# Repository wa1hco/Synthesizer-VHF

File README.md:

# Synthesizer-VHF

An ADF4351 synthesizer, 35 MHz to 4.4 GHz, with an ATtiny3216-M and USB. This branch, `hammond-1550Q`, is the Hammond 1550Q version: the board is the lid of the box. Designed by Jeffrey Millar (WA1HCO).

The first board in this repository was built and sent to fab with a TCXO, two RF outputs, USB serial, and a 12 V input. SPI between the microcontroller and the PLL is wired to ordinary pins, and the firmware bit-bangs it. That built board is the `as-built` branch. `main` carries the later layout of that same board, including the four-layer stackup and the 50 ohm coplanar RF routes. `hammond-1550Q` is the new enclosure and a new 10 MHz reference chain. It has not been built. The previous lid design remains on `diecast-2x2`.

Open the board from `hardware/Synthesizer-VHF.kicad_pro`. The project is KiCad 10.

## hammond-1550Q

The PCB is the lid of a Hammond 1550Q. Parts sit on the inside face. The SMA connectors sit on the outside face. USB-C J1 is on the inside face and does not overhang the outline. A contact strip on the rim ties the board ground to the box. Four mounting holes (H1–H4) match the 1550Q M3.5-0.6 pattern, 50 mm by 45 mm, with 4.10 mm clearance holes, and are bonded to ground.

The synthesizer is an ADF4351. Its VCO covers 2.2–4.4 GHz, and the on-chip divider brings the outputs down to 35 MHz. Two RF jacks leave the box.

The reference is an external 10 MHz on REF IN, shared when several boards must stay together. An on-board 10 MHz TCXO is the fallback. REF IN is 51 ohm and is squared before a 2:1 mux; the TCXO is squared the same way and is the other mux input. With no firmware, a pulldown on PA6 selects the TCXO. Firmware counts edges on PA5 to see that an external reference is present, then drives PA6 to select it. There is no ADF4002 and no REF OUT.

The schematic controller value is ATtiny3216-M. The footprint is the ATtiny1616 VQFN-20, 3 mm by 3 mm. ATtiny3216-M is not sold in that package. The symbol is still ATtiny1616-M. Its description says 32 kB flash. ATtiny3226-MF fits this footprint and has 32 kB flash. It is not a hex drop-in. The firmware still builds for an ATtiny1616. An FT231X provides USB-C serial. The first program is Optiboot over UPDI on scope loop TP1. After that, a USB plug-in starts Optiboot. DTR through C13 does not. Lock detect is scope loop TP6. Mux, DBG1, DBG2, MCU 3.3 V, and a scope ground are the same kind of loop. Ground for a probe is that ground loop.

Power is 5 V from USB. Three LP5907 regulators make 3.3 V. U10 is VREF for the reference chain. U8 is VVCO. U7 is VRF. FB2 feeds VDD from VRF. VDD supplies the controller, the FT231X VCCIO, and the ADF4351 DVDD and SDVDD pins.

Four reverse-mount LEDs shine through the lid: power, USB activity, reference lock, and synthesizer lock. H_LED1–H_LED4 are the light-pipe holes under those LEDs. They are plated, not filled, not tented, with no solder mask, so the bare copper finish stays visible. They are parked off the board until placed.

## Intended uses

Microwave transverter local oscillators, from 1296 MHz through 47 GHz, with external multipliers where the band is above the ADF4351. The synthesizer runs integer-N with a 10 MHz phase-detector frequency when the VCO lands on a 10 MHz multiple, and a small fractional modulus otherwise. The output divider stays at 1 when the wanted frequency is already inside 2.2–4.4 GHz.

SSB amplifier IMD testing, with several boards sharing the 10 MHz reference so the tones stay synchronized. That mode uses a finer fractional-N step and checks that fractional and integer-boundary spurs do not land on the IM3 products.

Both modes are described in `software/FIRMWARE-PLAN.md`. Any phase-noise numbers in that plan are estimates. This board has no measured phase noise.

## Status

The hammond-1550Q hardware is in layout. The schematic is the working design; the board has not been built or tested.

The firmware in this branch is still the as-built firmware. It assumes a 25 MHz reference. The rework for the 10 MHz reference, the two operating modes, and the lock behavior is planned in `software/FIRMWARE-PLAN.md` and is not done yet.

## Branches

- `main` — the original board, with the layout work that followed the fab order (stackup and 50 ohm RF routing).
- `as-built` — the board that was built, and the firmware written for it.
- `hammond-1550Q` — this Hammond 1550Q variant. Schematic in progress toward a new layout; firmware not yet moved off the 25 MHz design. `diecast-2x2` keeps the earlier 1590LB lid.

## Directory layout

- `hardware/` — KiCad project (`Synthesizer-VHF.kicad_pro`), design rules, the phase-noise spreadsheet, and fabrication-toolkit options.
- `hardware/libraries/` — project symbol and footprint libraries. See Libraries below.
- `hardware/datasheets/` — component datasheets.
- `hardware/jlcpcb/` — fab outputs committed with the board (drill maps and the fabrication-toolkit database). New files generated into that directory are left untracked.
- `software/` — PlatformIO firmware for the ATtiny1616. `src/` and `include/` are the firmware, `lib/` is for private libraries, and `algorithms/` holds the fractional-N notes.
- `scripts/` — build, flash, and host-test launchers.

## Libraries

Project libraries sit next to the board. The library tables refer to them with `${KIPRJMOD}`:

- `hardware/libraries/Synthesizer.kicad_sym` — project symbols. The ADP150 symbol remains from the first board. This variant uses LP5907 regulators.
- `hardware/libraries/adf4350.kicad_sym` — ADF4350 symbol.
- `hardware/libraries/Synthesizer.pretty` — the footprints that are not in KiCad's libraries: the reverse-mount Kingbright LEDs, the 1550Q mounting holes, the LED light-pipe holes, and the G-Switch USB-C receptacle. 0402 parts, the ADF4351 LFCSP, the 3225 oscillator, and the scope loops use KiCad's own footprints.

Passives, connectors, the ATtiny1616-M symbol, the FT231X, and their 3D shapes come from KiCad's standard libraries. Where a footprint has a 3D model, the path uses `${KICAD8_3DMODEL_DIR}`. KiCad 10 resolves that older name to its own 3D library (`KICAD10_3DMODEL_DIR`) unless `KICAD8_3DMODEL_DIR` is set on its own. This board has no separate project 3D model. The old MAX2870 download is not used, so it is not in the library tables.

KiCad 10 may warn that some standard symbols and footprints differ from the copies stored in the schematic and board. Those stored copies are the ones the layout uses.

## Build the firmware

Install [PlatformIO](https://platformio.org/). From the repository root, run:

```
scripts/build-firmware
```

That builds `software/` for an ATtiny1616 at 20 MHz on the internal oscillator.

The host check of the ADF4351 register math, with no board attached, is:

```
scripts/test-adf4351
```

## Flash the firmware

The first boards need Optiboot installed over UPDI before the USB port can load an application. The adapter wiring, fuse values, and avrdude command are in `software/INITIAL-PROGRAMMING.md`.

`scripts/flash-firmware` runs `pymcuprog` on the FT231X port in `software/platformio.ini`. That port is the application UART. It does not program Optiboot.

Scope loop TP1 is UPDI. TP6 is lock detect. Use the scope ground loop with the UPDI loop.

The current firmware still speaks the as-built serial console at 57600 baud. Single keys change the output:

| Key | Effect |
| --- | --- |
| `x` / `c` | −10 Hz / +10 Hz |
| `s` / `d` | −100 Hz / +100 Hz |
| `w` / `e` | −1 kHz / +1 kHz |
| `2` / `3` | −10 kHz / +10 kHz |
| `1` / `4` | −100 kHz / +100 kHz |
| `5` / `6` | −10 MHz / +10 MHz |
| `/` | toggle the RF output |
| `m` | cycle the ADF4351 muxout setting |

That console is the 25 MHz firmware. The hammond-1550Q behavior is the plan in `software/FIRMWARE-PLAN.md`.

## Older checkouts

Commit or stash any edits to `Hardware/Synthesizer-VHF.kicad_pcb` before updating a very old checkout. That file lives at `hardware/Synthesizer-VHF.kicad_pcb`.

## License

- Software (`software/`, `scripts/`): GPL-3.0-or-later. See `LICENSE`.
- Hardware design files (`hardware/`): CERN-OHL-S-2.0. See `LICENSE-HARDWARE`.

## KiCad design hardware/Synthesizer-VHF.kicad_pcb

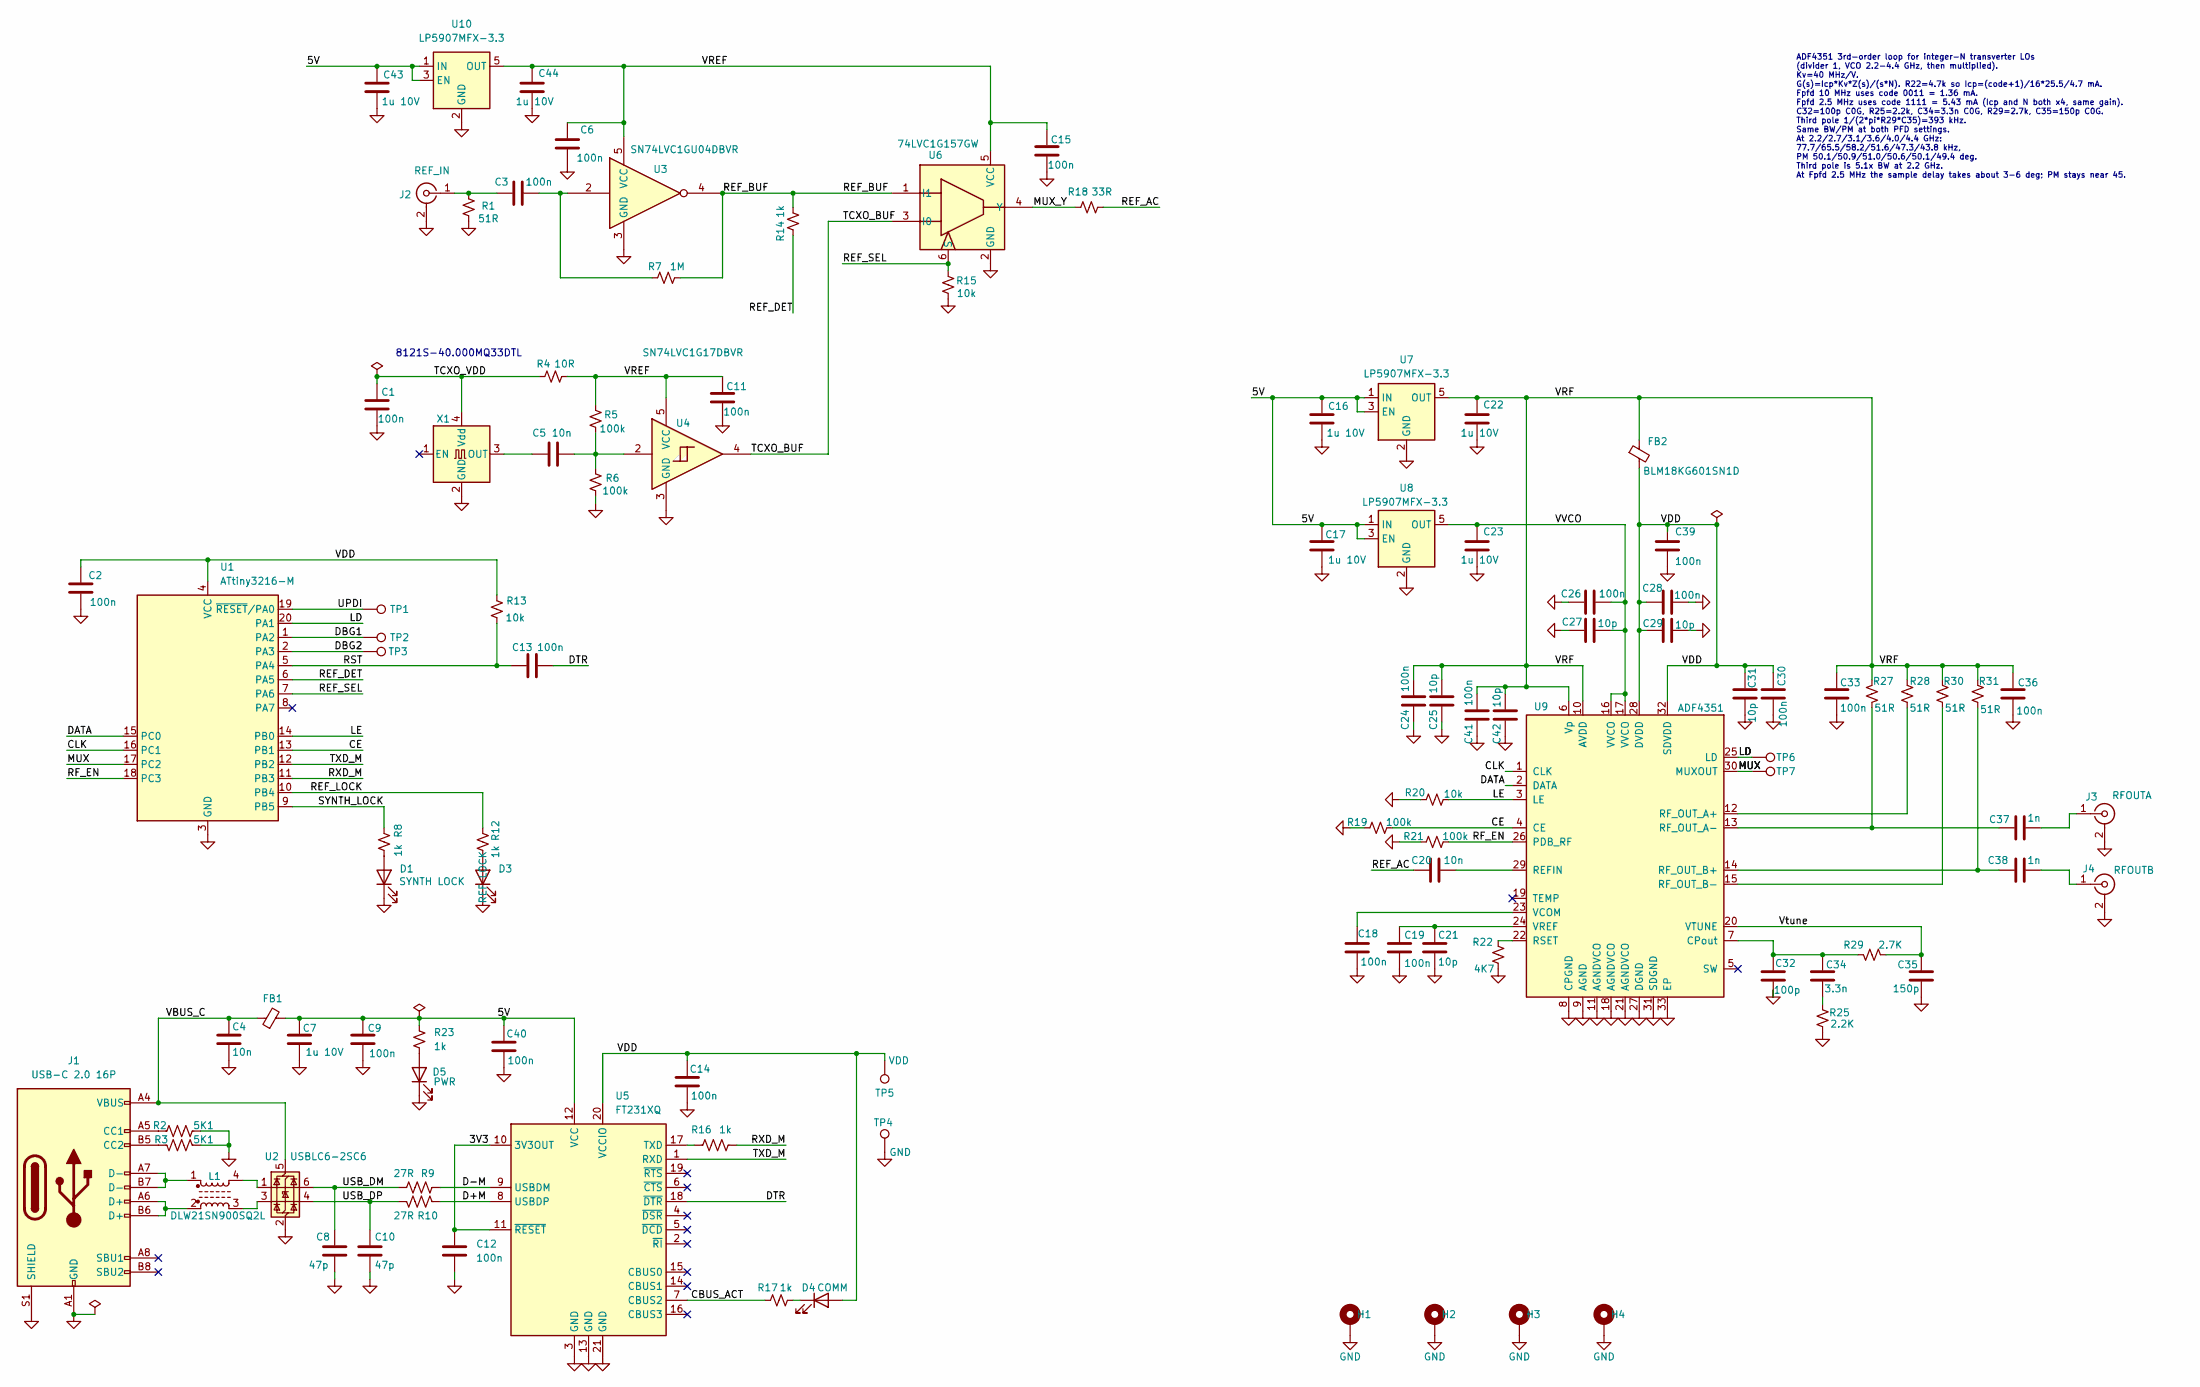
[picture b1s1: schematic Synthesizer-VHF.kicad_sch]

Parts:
C1, C2, C3, C6, C11, C12, C13, C14, C15, C18, C19, C24, C26, C28, C30, C33, C36, C40, C41: 100n; C_0402_1005Metric; LCSC C1525
C4: 10n; C_0402_1005Metric; LCSC C1546
C5, C20: 10n; C_0402_1005Metric; LCSC C15195
C7, C16, C17, C22, C23, C43, C44: 1u 10V; C_0402_1005Metric; LCSC C52923
C8, C10: 47p; C_0402_1005Metric; LCSC C1567
C9: 100n; C_0402_1005Metric; LCSC C1546
C21, C25, C27, C29, C31, C42: 10p; C_0402_1005Metric; LCSC C32949
C32: 100p; C_0402_1005Metric; LCSC C14665
C34: 3.3n; C_0402_1005Metric; LCSC C107048
C35: 150p; C_0402_1005Metric; LCSC C107038
C37, C38: 1n; C_0402_1005Metric; LCSC C76947
C39: 100n; C_0402_1005Metric; LCSC C32949
D1, D3: Red_LED; LED_KPTL-3216_ReverseMount; LCSC C598393
D4, D5: Green_LED; LED_KPTL-3216_ReverseMount; LCSC C598390
FB1, FB2: BLM18KG601SN1D; L_0603_1608Metric; LCSC C85833
H1, H2, H3, H4: M3.5; MountingHole_4.1mm_M3.5_Pad
J1: USB-C 2.0 16P; USB_C_Receptacle_G-Switch_GT-USB-7010ASV; LCSC C2988369
J2: REF_IN; SMA_Amphenol_901-144_Vertical; MPN 142-0701-801; LCSC C496551
J3: RFOUTA; SMA_Amphenol_901-144_Vertical; LCSC C496551
J4: RFOUTB; SMA_Amphenol_901-144_Vertical; LCSC C496551
L1: DLW21SN900SQ2L; L_CommonModeChoke_Coilank_ACM2012; LCSC C97856
R1: 51R; R_0402_1005Metric; MPN 0603WAF510JT5E; LCSC C23197
R2, R3: 5K1; R_0402_1005Metric; LCSC C105872
R4: 10R; R_0402_1005Metric; LCSC C25077
R5, R6: 100k; R_0402_1005Metric; LCSC C60491
R7: 1M; R_0402_1005Metric; LCSC C22553
R8, R12, R14, R16, R17, R23: 1k; R_0402_1005Metric; LCSC C11702
R9, R10: 27R; R_0402_1005Metric; LCSC C93929
R13, R15: 10k; R_0402_1005Metric; LCSC C60490
R18: 33R; R_0402_1005Metric; LCSC C25105
R19, R21: 100k; R_0402_1005Metric; LCSC C25803
R20: 10k; R_0402_1005Metric; LCSC C25804
R22: 4K7; R_0402_1005Metric; LCSC C105871
R25: 2.2K; R_0402_1005Metric; LCSC C4190
R27, R28, R30, R31: 51R; R_0402_1005Metric; LCSC C137960
R29: 2.7K; R_0402_1005Metric; LCSC C13167
TP1: UPDI; TestPoint_Keystone_5015_Micro_Mini; LCSC C5199798
TP2: DBG1; TestPoint_Keystone_5015_Micro_Mini; LCSC C5199798
TP3: DBG2; TestPoint_Keystone_5015_Micro_Mini; LCSC C5199798
TP4: GND; TestPoint_Keystone_5015_Micro_Mini; LCSC C5199798
TP5: VDD; TestPoint_Keystone_5015_Micro_Mini; LCSC C5199798
TP6: LD; TestPoint_Keystone_5015_Micro_Mini; LCSC C5199798
TP7: MUX; TestPoint_Keystone_5015_Micro_Mini; LCSC C5199798
U1: ATtiny3216-M; VQFN-20-1EP_3x3mm_P0.4mm_EP1.7x1.7mm; LCSC C507118
U2: USBLC6-2SC6; SOT-23-6; LCSC C7519
U3: SN74LVC1GU04DBVR; SOT-23-5; MPN SN74LVC1GU04DBVR; LCSC C81934
U4: SN74LVC1G17DBVR; SOT-23-5; LCSC C7836
U5: FT231XQ; QFN-20-1EP_4x4mm_P0.5mm_EP2.5x2.5mm; LCSC C132159
U6: 74LVC1G157GW; SOT-363_SC-70-6; LCSC C135822
U7, U8, U10: LP5907MFX-3.3; SOT-23-5; LCSC C80670
U9: ADF4351; LFCSP-32-1EP_5x5mm_P0.5mm_EP3.25x3.25mm; LCSC C654681
X1: 8121S-40.000MQ33DTL; Crystal_SMD_2016-4Pin_2.0x1.6mm; LCSC C22435063

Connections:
/3V3: C12.1, U5.10 (3V3OUT), U5.11 (~RESET)
/5V: C7.1, C9.1, C16.1, C17.1, C40.1, C43.1, FB1.2, R23.1, U5.12 (VCC), U7.1 (IN), U7.3 (EN), U8.1 (IN), U8.3 (EN), U10.1 (IN), U10.3 (EN)
/CBUS_ACT: R17.2, U5.7 (CBUS2)
/CE: R19.1, U1.13 (PB1), U9.4 (CE)
/CLK: U1.16 (PC1), U9.1 (CLK)
/D+M: R10.1, U5.8 (USBDP)
/D-M: R9.1, U5.9 (USBDM)
/DATA: U1.15 (PC0), U9.2 (DATA)
/DBG1: TP2.1 (1_1), U1.1 (PA2)
/DBG2: TP3.1 (1_1), U1.2 (PA3)
/DTR: C13.1, U5.18 (~DTR)
/LD: TP6.1 (1_1), U1.20 (PA1), U9.25 (LD)
/LE: R20.1, U1.14 (PB0), U9.3 (LE)
/MUX: TP7.1 (1_1), U1.17 (PC2), U9.30 (MUXOUT)
/MUX_Y: R18.1, U6.4 (Y)
/REF_AC: C20.2, R18.2
/REF_BUF: R7.2, R14.1, U3.4, U6.1 (I1)
/REF_DET: R14.2, U1.6 (PA5)
/REF_LOCK: R12.1, U1.10 (PB4)
/REF_SEL: R15.1, U1.7 (PA6), U6.6 (S)
/RF_EN: R21.1, U1.18 (PC3), U9.26 (PDB_RF)
/RST: C13.2, R13.2, U1.5 (PA4)
/RXD_M: R16.2, U1.11 (PB3)
/SYNTH_LOCK: R8.1, U1.9 (PB5)
/TCXO_BUF: U4.4, U6.3 (I0)
/TCXO_VDD: C1.1, R4.2, X1.4 (Vdd)
/TXD_M: U1.12 (PB2), U5.1 (RXD)
/UPDI: TP1.1 (1_1), U1.19 (~RESET/PA0)
/USB_DM: C8.1, R9.2, U2.6 (I/O1)
/USB_DP: C10.1, R10.2, U2.4 (I/O2)
/VBUS_C: C4.1, FB1.1, J1.A4 (VBUS), J1.A9 (VBUS), J1.B4 (VBUS), J1.B9 (VBUS), U2.5 (VBUS)
/VDD: C2.1, C14.1, C28.1, C29.2, C30.1, C31.2, C39.1, D4.2 (A), FB2.2, R13.1, TP5.1 (1_1), U1.4 (VCC), U5.20 (VCCIO), U9.28 (DVDD), U9.32 (SDVDD)
/VREF: C6.1, C11.1, C15.1, C44.1, R4.1, R5.1, U3.5 (VCC), U4.5 (VCC), U6.5 (VCC), U10.5 (OUT)
/VRF: C22.1, C24.1, C25.1, C33.1, C36.1, C41.1, C42.1, FB2.1, R27.2, R28.2, R30.2, R31.2, U7.5 (OUT), U9.6 (Vp), U9.10 (AVDD)
/VVCO: C23.1, C26.1, C27.2, U8.5 (OUT), U9.16 (VVCO), U9.17 (VVCO)
/Vtune: C35.1, R29.2, U9.20 (VTUNE)
GND: C1.2, C2.2, C4.2, C6.2, C7.2, C8.2, C9.2, C10.2, C11.2, C12.2, C14.2, C15.2, C16.2, C17.2, C18.2, C19.2, C21.2, C22.2, C23.2, C24.2, C25.2, C26.2, C27.1, C28.2, C29.1, C30.2, C31.1, C32.2, C33.2, C35.2, C36.2, C39.2, C40.2, C41.2, C42.2, C43.2, C44.2, D1.1 (K), D3.1 (K), D5.1 (K), H1.1 (1_1), H2.1 (1_1), H3.1 (1_1), H4.1 (1_1), J1.A1 (GND), J1.A12 (GND), J1.B1 (GND), J1.B12 (GND), J1.S1 (SHIELD), J2.2 (Ext), J3.2 (Ext), J4.2 (Ext), R1.2, R2.1, R3.1, R6.2, R15.2, R19.2, R20.2, R21.2, R22.1, R25.2, TP4.1 (1_1), U1.3 (GND), U1.21 (GND), U2.2 (GND), U3.3 (GND), U4.3 (GND), U5.3 (GND), U5.13 (GND), U5.21 (GND), U6.2 (GND), U7.2 (GND), U8.2 (GND), U9.8 (CPGND), U9.9 (AGND), U9.11 (AGNDVCO), U9.18 (AGNDVCO), U9.21 (AGNDVCO), U9.27 (DGND), U9.31 (SDGND), U9.33 (EP), U10.2 (GND), X1.2 (GND)
unnamed: C3.1, R7.1, U3.2
unnamed: C5.2, R5.2, R6.1, U4.2
unnamed: C34.2, R25.1
unnamed: D1.2 (A), R8.2
unnamed: D3.2 (A), R12.2
unnamed: D4.1 (K), R17.1
unnamed: D5.2 (A), R23.2
unnamed: J1.A5 (CC1), R2.2
unnamed: J1.B5 (CC2), R3.2
unnamed: J1.A6 (D+), J1.B6 (D+), L1.2
unnamed: J1.A7 (D-), J1.B7 (D-), L1.1
unnamed: C3.2, J2.1 (In), R1.1
unnamed: C37.2, J3.1 (In)
unnamed: C38.2, J4.1 (In)
unnamed: L1.3, U2.3 (I/O2)
unnamed: L1.4, U2.1 (I/O1)
unnamed: R16.1, U5.17 (TXD)
unnamed: C32.1, C34.1, R29.1, U9.7 (CPout)
unnamed: C20.1, U9.29 (REFIN)
unnamed: R28.1, U9.12 (RF_OUT_A+)
unnamed: C37.1, R27.1, U9.13 (RF_OUT_A-)
unnamed: C38.1, R31.1, U9.14 (RF_OUT_B+)
unnamed: R30.1, U9.15 (RF_OUT_B-)
unnamed: R22.2, U9.22 (RSET)
unnamed: C18.1, U9.23 (VCOM)
unnamed: C19.1, C21.1, U9.24 (VREF)
unnamed: C5.1, X1.3 (OUT)

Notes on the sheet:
8121S-40.000MQ33DTL
ADF4351 3rd-order loop for integer-N transverter LOs (divider 1, VCO 2.2-4.4 GHz, then multiplied). Kv=40 MHz/V. G(s)=Icp*Kv*Z(s)/(s*N). R22=4.7k so Icp=(code+1)/16*25.5/4.7 mA. Fpfd 10 MHz uses code 0011 = 1.36 mA. Fpfd 2.5 MHz uses code 1111 = 5.43 mA (Icp and N both x4, same gain). C32=100p C0G,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

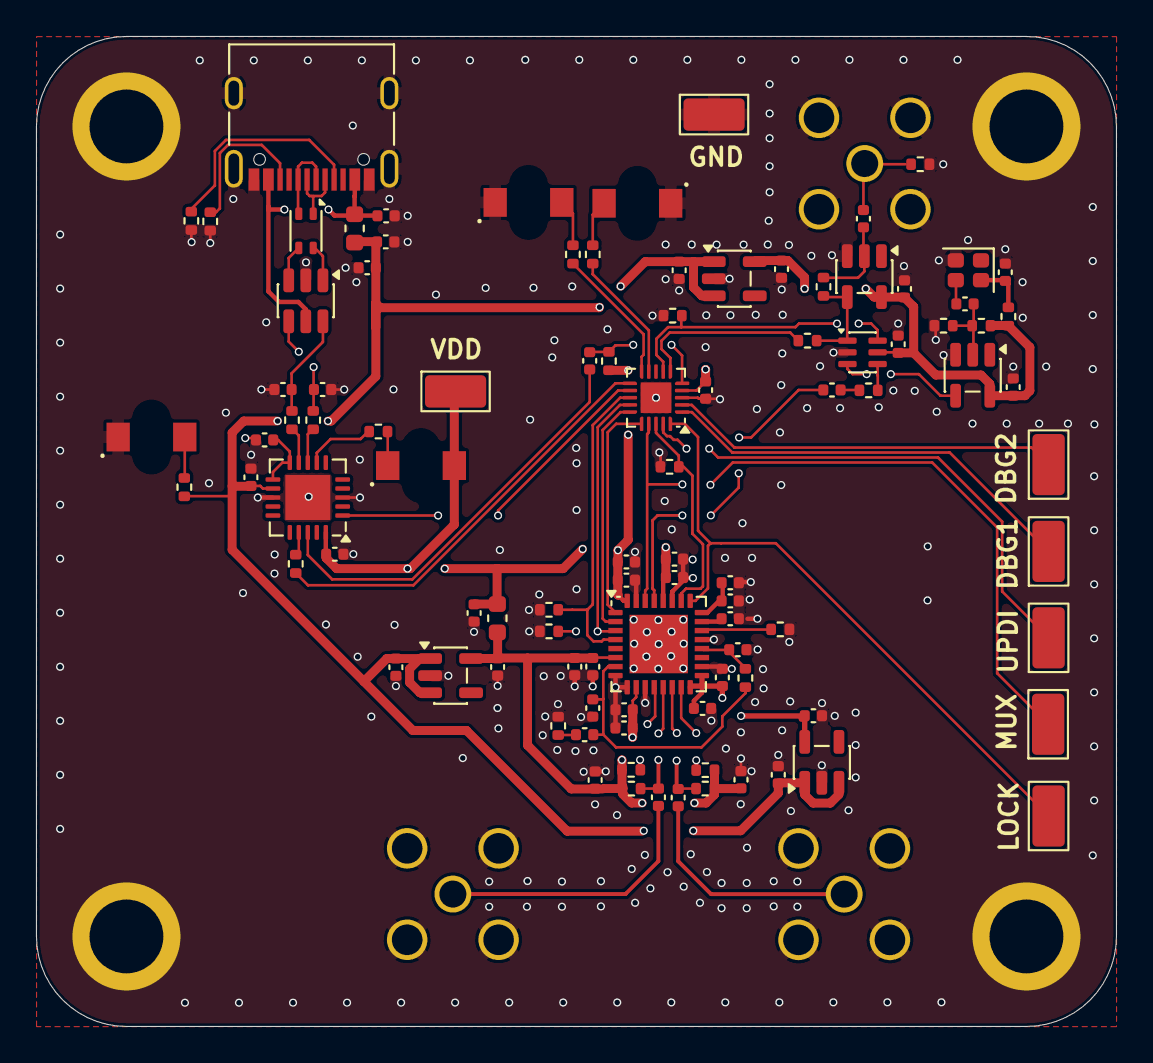
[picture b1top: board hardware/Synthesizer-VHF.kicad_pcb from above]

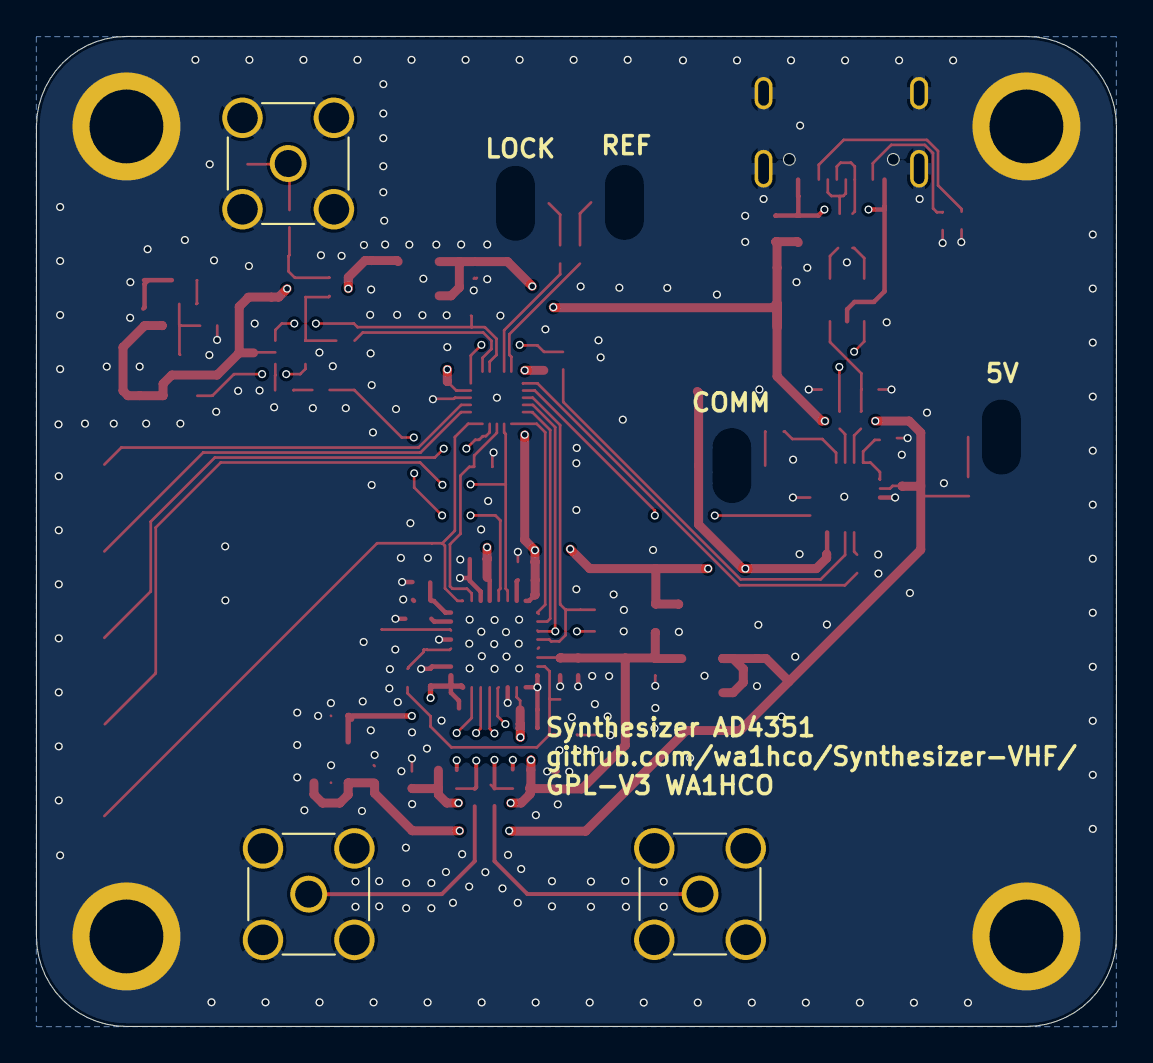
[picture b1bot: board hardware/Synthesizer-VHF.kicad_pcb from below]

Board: 4 copper layers, 60.0 x 55.0 mm, 105 parts (3 on the bottom side), 64 nets.

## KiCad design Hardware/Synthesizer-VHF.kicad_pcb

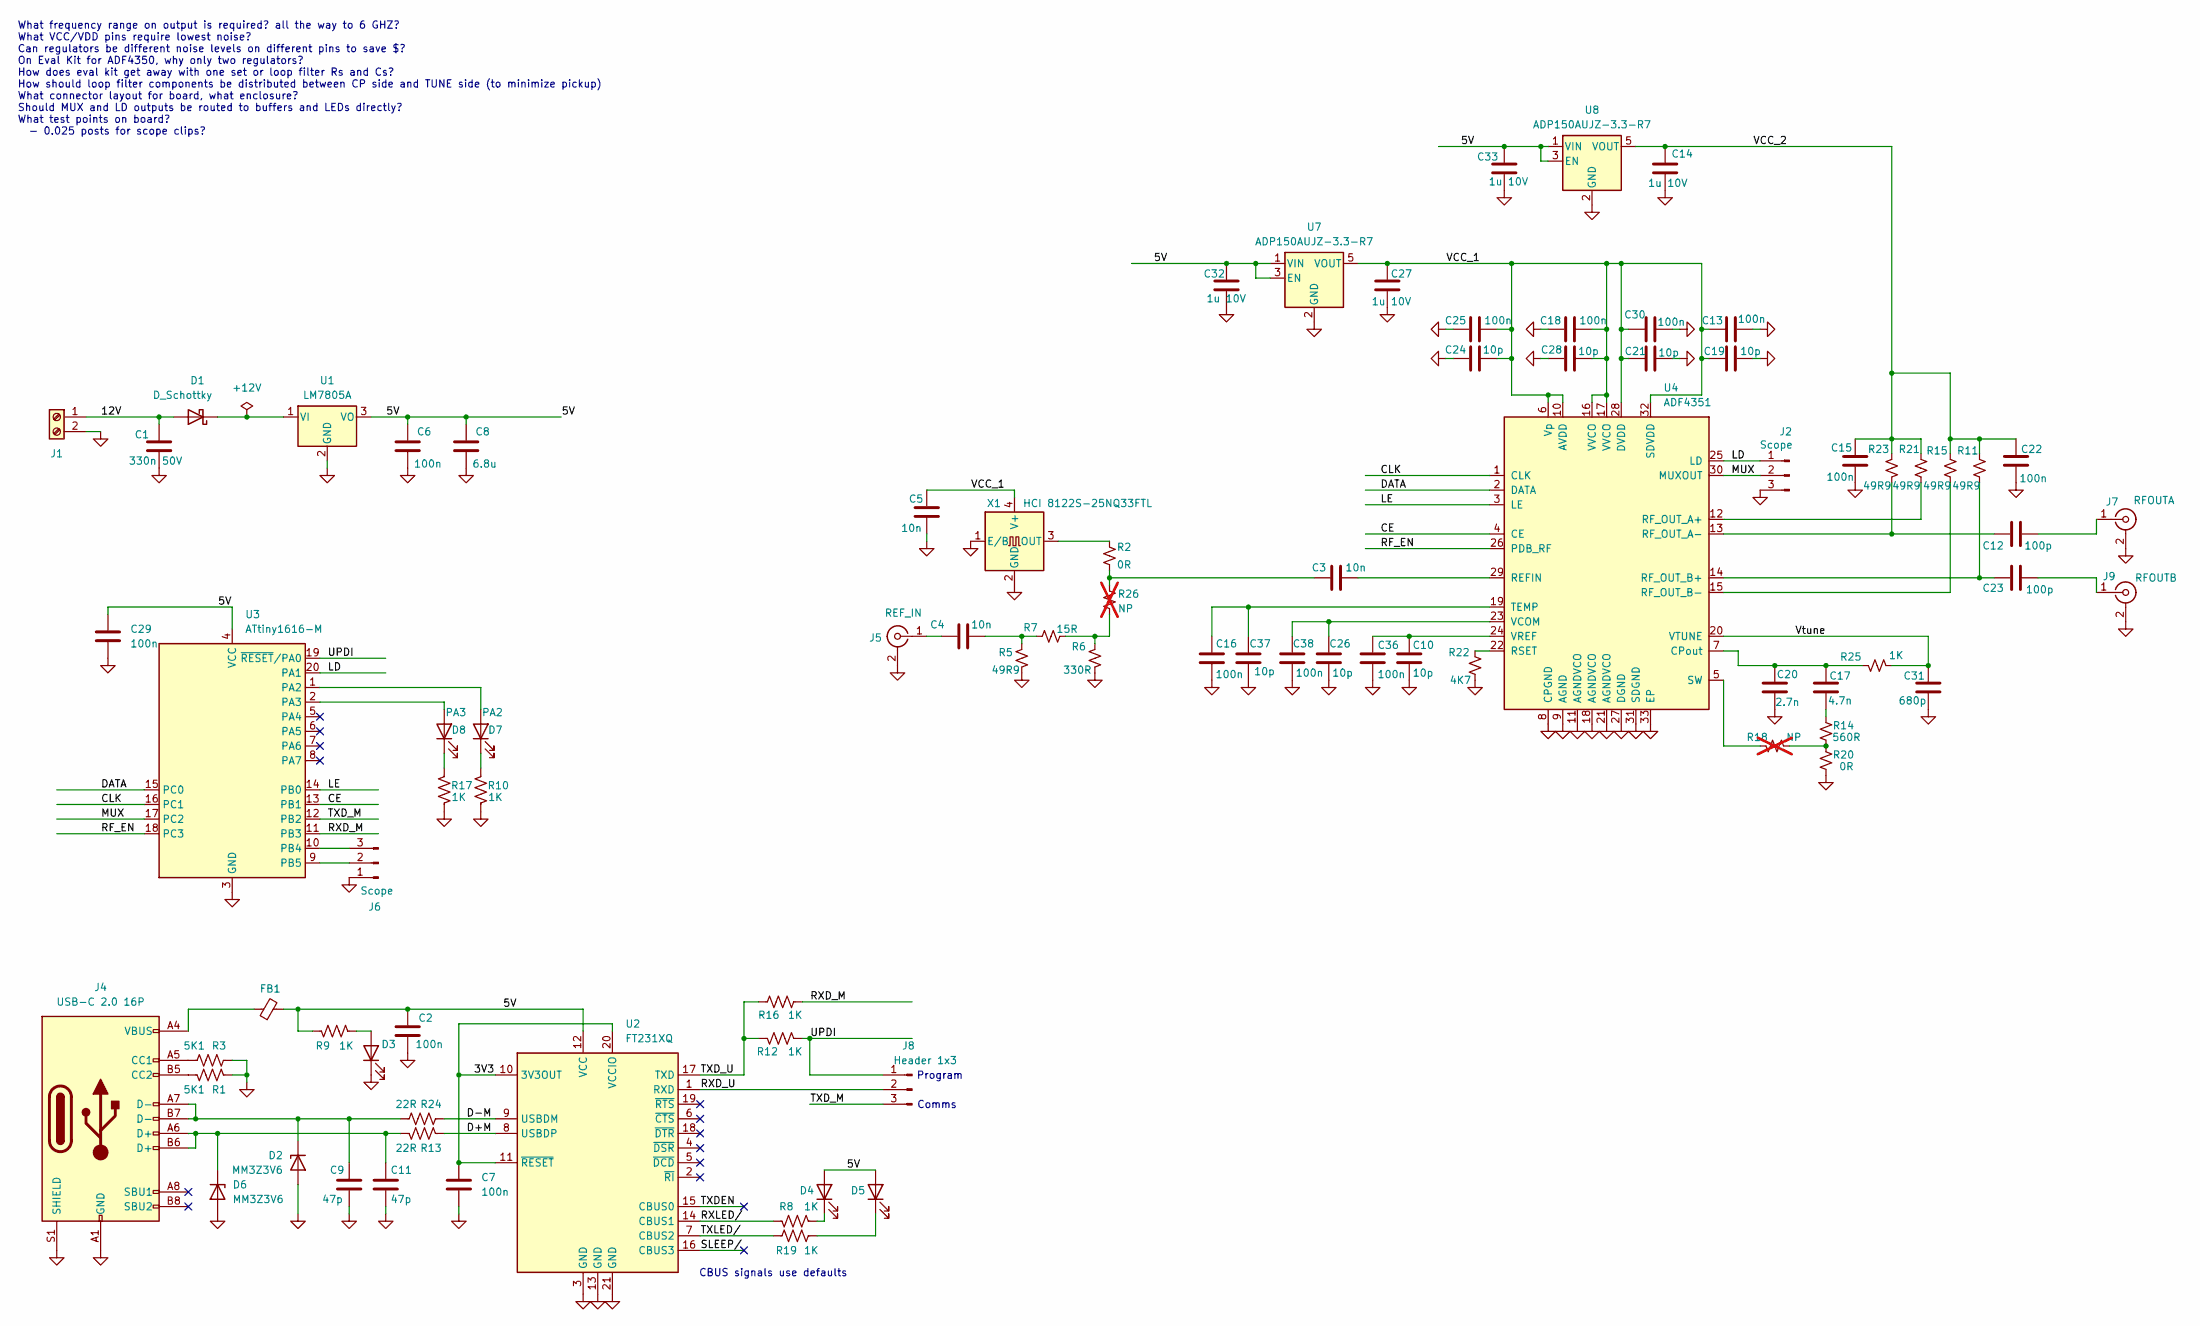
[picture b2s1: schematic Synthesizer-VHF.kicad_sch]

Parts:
C1: 330n 50V; C_0603_1608Metric; LCSC C282682
C2, C6, C7, C13, C15, C16, C18, C22, C25, C29, C30, C36, C38: 100n; Cap_0402; LCSC C1525
C3, C4, C5: 10n; Cap_0402; LCSC C15195
C8: 6.8u; C_0603_1608Metric; LCSC C338096
C9, C11: 47p; Cap_0402; LCSC C1567
C10, C19, C21, C24, C26, C28, C37: 10p; Cap_0402; LCSC C32949
C12, C23: 100p; Cap_0402; LCSC C1546
C14, C27, C32, C33: 1u 10V; Cap_0402; LCSC C52923
C17: 4.7n; C_0805_2012Metric; LCSC C513576
C20: 2.7n; C_0805_2012Metric; LCSC C541551
C31: 680p; C_0805_2012Metric; LCSC C107121
D1: D_Schottky; D_0603_1608Metric; LCSC C143772
D2, D6: MM3Z3V6; D_SOD-523; LCSC C22395574
D3: blue; LED_0402_1005Metric; LCSC C364550
D4, D5: Yellow; LED_0402_1005Metric; LCSC C434449
D7: PA2; LED_0402_1005Metric; LCSC C364550
D8: PA3; LED_0402_1005Metric; LCSC C364550
FB1: FerriteBead_Small; L_0805_2012Metric; LCSC C1017
J1: Screw_Terminal_01x02; TerminalBlock_TE_282834-2_1x02_P2.54mm_Horizontal; LCSC C5188442
J2, J6: Scope; PinHeader_1x03_P2.54mm_Vertical; LCSC C6332196
J4: USB-C 2.0 16P; USB_C_Receptacle_G-Switch_GT-USB-7010ASV; LCSC C2988369
J5: REF_IN; SMA_Amphenol_901-143_Horizontal; LCSC C496551
J7: RFOUTA; SMA_Amphenol_901-143_Horizontal; LCSC C496551
J8: Header 1x3; PinHeader_1x03_P2.54mm_Vertical; LCSC C6332196
J9: RFOUTB; SMA_Amphenol_901-143_Horizontal; LCSC C496551
R1, R3: 5K1; Res_0402; LCSC C105872
R2, R20: 0R; R_0805_2012Metric; LCSC C17168
R5, R11, R15, R21, R23: 49R9; Res_0402; LCSC C137960
R6: 330R; Res_0402; LCSC C105876
R7: 15R; Res_0402; LCSC C138052
R8, R9, R10, R12, R16, R17, R19: 1K; Res_0402; LCSC C11702
R13, R24: 22R; Res_0402; LCSC C93929
R14: 560R; R_0805_2012Metric; LCSC C114536
R18: NP; R_0805_2012Metric; not fitted
R22: 4K7; Res_0402; LCSC C105871
R25: 1K; R_0805_2012Metric; LCSC C17513
R26: NP; R_0805_2012Metric; LCSC C17168; not fitted
U1: LM7805A; TO-252-2; LCSC C5145267
U2: FT231XQ; QFN-20-1EP_4x4mm_P0.5mm_EP2.5x2.5mm; LCSC C132159
U3: ATtiny1616-M; VQFN-20-1EP_3x3mm_P0.4mm_EP1.7x1.7mm; LCSC C507118
U4: ADF4351; LFCSP-32-1EP_5x5mm_P0.5mm_EP3.25x3.25mm; LCSC C654681
U7, U8: ADP150AUJZ-3.3-R7; SOT-23-5; LCSC C29149
X1: HCI 8122S-25NQ33FTL; Oscillator_SMD2520; LCSC C20623084

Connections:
/3V3: C7.1, U2.10 (3V3OUT), U2.11 (~RESET), U2.20 (VCCIO)
/5V: C2.1, C6.1, C8.1, C29.1, C32.1, C33.1, D4.2 (A), D5.2 (A), FB1.2, R9.2, U1.3 (VO), U2.12 (VCC), U3.4 (VCC), U7.1 (VIN), U7.3 (EN), U8.1 (VIN), U8.3 (EN)
/12V: C1.1, D1.2 (A), J1.1
/CE: U3.13 (PB1), U4.4 (CE)
/CLK: U3.16 (PC1), U4.1 (CLK)
/D+M: R13.1, U2.8 (USBDP)
/D-M: R24.1, U2.9 (USBDM)
/DATA: U3.15 (PC0), U4.2 (DATA)
/LD: J2.1, U3.20 (PA1), U4.25 (LD)
/LE: U3.14 (PB0), U4.3 (LE)
/MUX: J2.2, U3.17 (PC2), U4.30 (MUXOUT)
/RF_EN: U3.18 (PC3), U4.26 (PDB_RF)
/RXD_M: R16.2, U3.11 (PB3)
/RXD_U: J8.2, U2.1 (RXD)
/RXLED/: R8.1, U2.14 (CBUS1)
/SLEEP/: U2.16 (CBUS3)
/TXDEN: U2.15 (CBUS0)
/TXD_M: J8.3, U3.12 (PB2)
/TXD_U: R12.1, R16.1, U2.17 (TXD)
/TXLED/: R19.1, U2.7 (CBUS2)
/UPDI: J8.1, R12.2, U3.19 (~RESET/PA0)
/VCC_1: C5.2, C13.1, C18.1, C19.2, C21.2, C24.1, C25.1, C27.1, C28.2, C30.1, U4.6 (Vp), U4.10 (AVDD), U4.16 (VVCO), U4.17 (VVCO), U4.28 (DVDD), U4.32 (SDVDD), U7.5 (VOUT), X1.4 (V+)
/VCC_2: C14.1, C15.1, C22.1, R11.2, R15.2, R21.2, R23.2, U8.5 (VOUT)
/Vtune: C31.1, R25.2, U4.20 (VTUNE)
GND: C1.2, C2.2, C5.1, C6.2, C7.2, C8.2, C9.2, C10.2, C11.2, C13.2, C14.2, C15.2, C16.1, C18.2, C19.1, C20.2, C21.1, C22.2, C24.2, C25.2, C26.2, C27.2, C28.1, C29.2, C30.2, C31.2, C32.2, C33.2, C36.2, C37.1, C38.2, D2.2 (A), D3.1 (K), D6.2 (A), J1.2, J2.3, J4.A1 (GND), J4.A12 (GND), J4.B1 (GND), J4.B12 (GND), J4.S1 (SHIELD), J5.2 (Ext), J6.1, J7.2 (Ext), J9.2 (Ext), R1.1, R3.1, R5.2, R6.2, R10.2, R17.2, R20.2, R22.1, U1.2 (GND), U2.3 (GND), U2.13 (GND), U2.21 (GND), U3.3 (GND), U3.21 (GND), U4.8 (CPGND), U4.9 (AGND), U4.11 (AGNDVCO), U4.18 (AGNDVCO), U4.21 (AGNDVCO), U4.27 (DGND), U4.31 (SDGND), U4.33 (EP), U7.2 (GND), U8.2 (GND), X1.1 (E/B), X1.2 (GND)
unnamed: C3.2, R2.2, R26.1
unnamed: C4.1, R5.1, R7.1
unnamed: C17.2, R14.1
unnamed: D1.1 (K), U1.1 (VI)
unnamed: C9.1, D2.1 (K), J4.A7 (D-), J4.B7 (D-), R24.2
unnamed: D3.2 (A), R9.1
unnamed: D4.1 (K), R8.2
unnamed: D5.1 (K), R19.2
unnamed: C11.1, D6.1 (K), J4.A6 (D+), J4.B6 (D+), R13.2
unnamed: D7.2 (A), U3.1 (PA2)
unnamed: D7.1 (K), R10.1
unnamed: D8.2 (A), U3.2 (PA3)
unnamed: D8.1 (K), R17.1
unnamed: FB1.1, J4.A4 (VBUS), J4.A9 (VBUS), J4.B4 (VBUS), J4.B9 (VBUS)
unnamed: J4.A5 (CC1), R3.2
unnamed: J4.B5 (CC2), R1.2
unnamed: C4.2, J5.1 (In)
unnamed: J6.2, U3.9 (PB5)
unnamed: J6.3, U3.10 (PB4)
unnamed: C12.2, J7.1 (In)
unnamed: C23.2, J9.1 (In)
unnamed: R14.2, R18.1, R20.1
unnamed: R6.1, R7.2, R26.2
unnamed: C17.1, C20.1, R25.1, U4.7 (CPout)
unnamed: C3.1, U4.29 (REFIN)
unnamed: R21.1, U4.12 (RF_OUT_A+)
unnamed: C12.1, R23.1, U4.13 (RF_OUT_A-)
unnamed: C23.1, R11.1, U4.14 (RF_OUT_B+)
unnamed: R15.1, U4.15 (RF_OUT_B-)
unnamed: R22.2, U4.22 (RSET)
unnamed: R18.2, U4.5 (SW)
unnamed: C16.2, C37.2, U4.19 (TEMP)
unnamed: C26.1, C38.1, U4.23 (VCOM)
unnamed: C10.1, C36.1, U4.24 (VREF)
unnamed: R2.1, X1.3 (OUT)

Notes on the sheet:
Comms
CBUS signals use defaults
What frequency range on output is required? all the way to 6 GHZ? What VCC/VDD pins require lowest noise? Can regulators be different noise levels on different pins to save $? On Eval Kit for ADF4350, why only two regulators? How does eval kit get away with one set or loop filter Rs and Cs? How sho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
Program

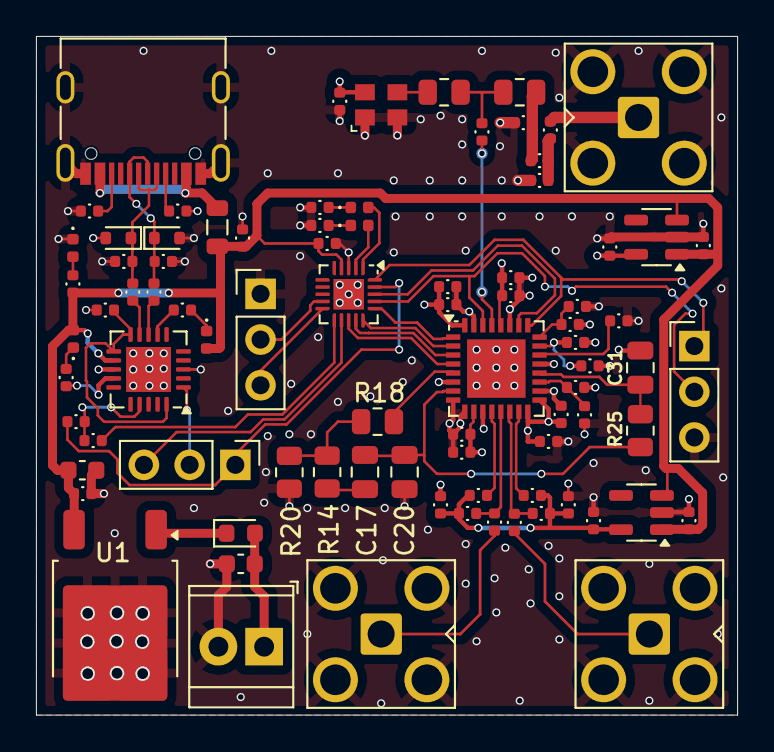
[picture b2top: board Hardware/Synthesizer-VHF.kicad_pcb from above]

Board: 4 copper layers, 38.9 x 37.7 mm, 85 parts (0 on the bottom side), 58 nets.

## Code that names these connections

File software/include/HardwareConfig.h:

// SPDX-License-Identifier: GPL-3.0-or-later
#ifndef HardwareConfig_h
#define HardwareConfig_h

#include <Arduino.h> // get the pin names
#include "Config.h"

//  ATTinyX16, QFN-20, Hardware Pin Definitions, lower case means secondary pin location
//----------|---|---|---|---|---|---|---|---|---|---|---|---|---|---|---|---|---|---|---|---|
// Chip Pin |1  |2  |3  |4  |5  |6  |7  |8  |9  |10 |11 |12 |13 |14 |15 |16 |17 |18 |19 |20 |
// Port #   |15 |16 |   |   |0  |1  |2  |3  |4  |5  |6  |7  |6  |0  |10 |11 |12 |13 |17 |14 |
// Port     |PA2|PA3|GND|VCC|PA4|PA5|PA6|PA7|PB5|PB4|PB3|PB2|PB1|PB0|PC0|PC1|PC2|PC3|PA0|PA1|
//----------|---|---|---|---|---|---|---|---|---|---|---|---|---|---|---|---|---|---|---|---|
// Power    |   |   |GND|VCC|   |   |   |   |   |   |   |   |   |   |   |   |   |   |   |   |
// TCA0     |   |   |   |   |WO4|WO5|   |   |wo2|wo1|wo0|WO2|WO1|WO0|   |   |   |wo3|WO3|   |
// UPDI     |   |   |   |   |   |   |   |   |   |   |   |   |   |   |   |   |   |   |PDI|   |
// ADC0     |A2 |A3 |A2 |   |A4 |A5 |A6 |A7 |A8 |A9 |   |   |A10|A11|   |A17|A14|A15|A0 |A1 |
// ADC1     |   |   |   |   |A0 |A1 |A2 |A3 |   |   |   |   |   |   |A6 |A7 |A8 |A9 |   |   |
// TWI0     |scl|   |   |   |   |   |   |   |   |   |   |   |SDA|SCL|   |   |   |   |   |sda|
// USART0   |rxd|xck|   |   |   |   |   |   |   |   |RXD|TXD|XCK|DIR|   |   |   |   |   |txd|
// CLOCK    |   |EXT|   |   |   |   |   |   |   |   |OSC|OSC|   |   |   |   |   |   |   |   |
//----------|---|---|---|---|---|---|---|---|---|---|---|---|---|---|---|---|---|---|---|---|

// Sequencer board use of pins.
// This table is not the hammond-1550Q pin use.
// That pin use is in software/FIRMWARE-PLAN.md section 1.
// Current firmware still builds against the defines below.
//----------|---|---|---|---|---|---|---|---|---|---|---|---|---|---|---|---|---|---|---|---|
// Pins     |1  |2  |3  |4  |5  |6  |7  |8  |9  |10 |11 |12 |13 |14 |15 |16 |17 |18 |19 |20 |  
// Port     |PA2|PA3|GND|VCC|PA4|PA5|PA6|PA7|PB5|PB4|PB3|PB2|PB1|PB0|PC0|PC1|PC2|PC3|PA0|PA1|
//----------|---|---|---|---|---|---|---|---|---|---|---|---|---|---|---|---|---|---|---|---|  
// ADF4351  |   |   |   |   |   |   |   |   |   |   |   |   |CE |LE |DAT|CLK|MUX|EN |   |LD |
// Serial   |   |   |   |   |   |   |   |   |   |   |RXD|TXD|   |   |   |   |   |   |   |   |
// LED      |LED|LED|   |   |   |   |   |   |   |   |   |   |   |   |   |   |   |   |   |   |
// UPDI     |   |   |   |   |   |   |   |   |   |   |   |   |   |   |   |   |   |   |PDI|   |
// TstPts   |   |   |   |   |   |   |   |   |J32|J33|   |   |   |   |   |   |   |   |   |   |
//--------- |---|---|---|---|---|---|---|---|---|---|---|---|---|---|---|---|---|---|---|---|
// Unused   |   |   |   |   |5  |6  |7  |8  |   |   |   |   |13 |   |   |   |   |   |   |   |
//--------- |---|---|---|---|---|---|---|---|---|---|---|---|---|---|---|---|---|---|---|---|

// Hardware Connections for ATTinyX16
// Pin definitions 
//      Pin Name  Port      Name           
#define SCKPin    PIN_PC1   // CLK            
#define MOSIPin   PIN_PC0   // DATA           
#define SSPin     PIN_PB0   // LE            
#define RFENPin  PIN_PC3   // RF Enable   
#define MUXPin    PIN_PC2   // MUX input   
#define LDPin     PIN_PA1   // Lock Detect 
#define CEPin     PIN_PB1   // Chip Enable 
#define LEDD7Pin  PIN_PA2   // LED D7      
#define LEDD8Pin  PIN_PA3   // LED D8      
#define J6_3Pin   PIN_PB4   // J3_3        
#define J6_2Pin   PIN_PB5   // J3_2    

// Hardware design 
// defines how the optoisolators connect to MCU, 
// Steps are numbered from 0 to 3

// Public function
void InitPins();

#endif

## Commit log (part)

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2024-12-20 Schematic and layout of ADF4350 synthesizer with dual outputs, ATTiny1616, USB serial, and 12V input
2024-12-20 Added test points for scope probes, tweaked layout a bit
2024-12-20 Tried to find a better TCXO at 40 MHz, but jlcpcb froze all of kicad several times.
2025-01-04 Complete design used for pricing experient. 0.2 mm drilled vias cost a lot. had assembling through hole adds a lot 4 layers is is free Next up, climb the learning curve on 4 layer design price compon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
2025-01-07 Updated layout for 4 layer board as an experiment to check costs Changed low noise regulators to ADP150...used in the Eval board and fancy sig gen example Add more analysis to phase noise spreadsheet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
2025-01-07 final commit for 4 layer with parts on back side...that add a lot of cost Design uses a single supply with massive decoupling because EVKIT and Hellmich sig gen did it that way. Also parts on back si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
2025-01-07 fine tuning .gitignore
2025-01-07 Housekeeping
2025-01-08 Final version for costing and possible ordering Change TCXO to on available from LCSC
2025-01-14 This what got sent to fab. The wiring for SPI between MCU and ADF4351 is not connected to the hardware SPI pins and will need bit banging.
2025-01-14 clean up .gitignore, add software files
2025-01-23 Cleaned up early design files Commit as production branch for first version
2025-01-23 cleanup deleted files
2025-02-03 Adding userinterface for configuring synth
2025-02-04 Working towards saving registers in eeprom code to disassemble register fields into the global variables thinking about user commands
2025-02-09 work on user interface, gcd algorithm to find best Fpfd for integer N. Farey rational number search to find best MOD and FRAC for fractional N
2025-02-15 added rational number approximation to find FRAC/MOD for fractional N mode added greatest common divisor calculation to fine best combiation of N and R for integer N mode added printout of named regi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

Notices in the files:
hardware/Synthesizer-VHF.kicad_pcb:
GPL-V3 WA1HCO
